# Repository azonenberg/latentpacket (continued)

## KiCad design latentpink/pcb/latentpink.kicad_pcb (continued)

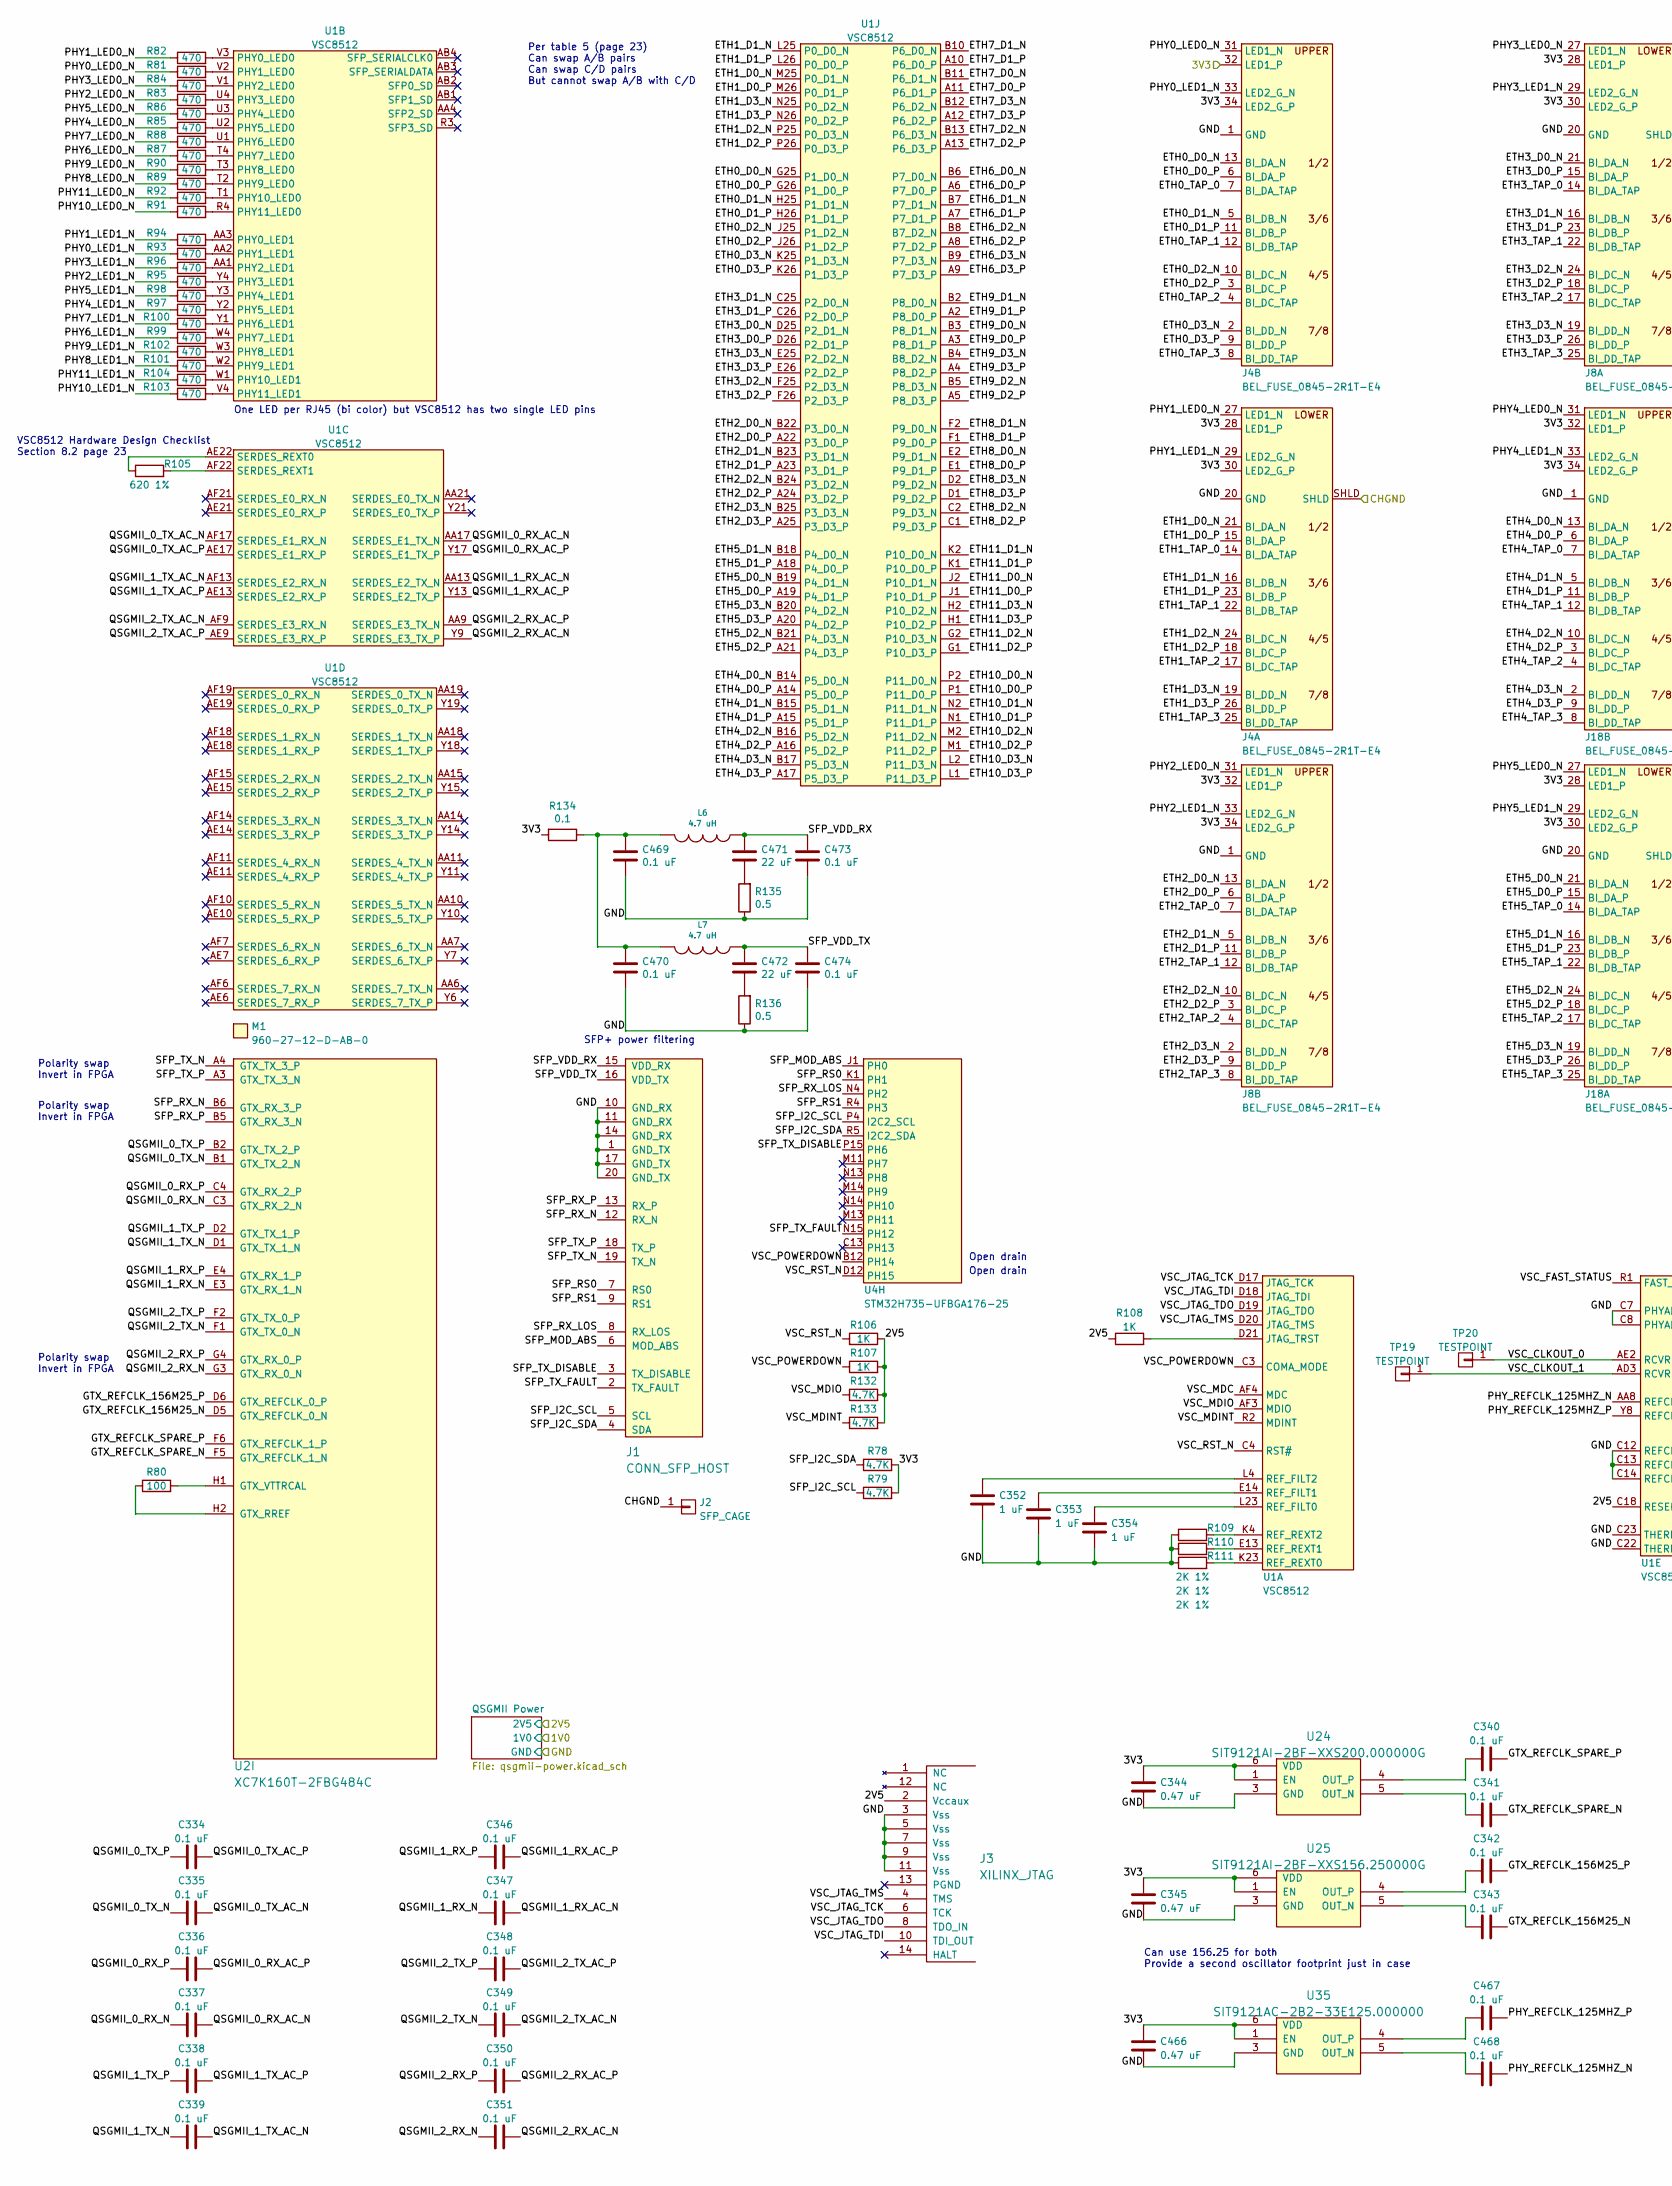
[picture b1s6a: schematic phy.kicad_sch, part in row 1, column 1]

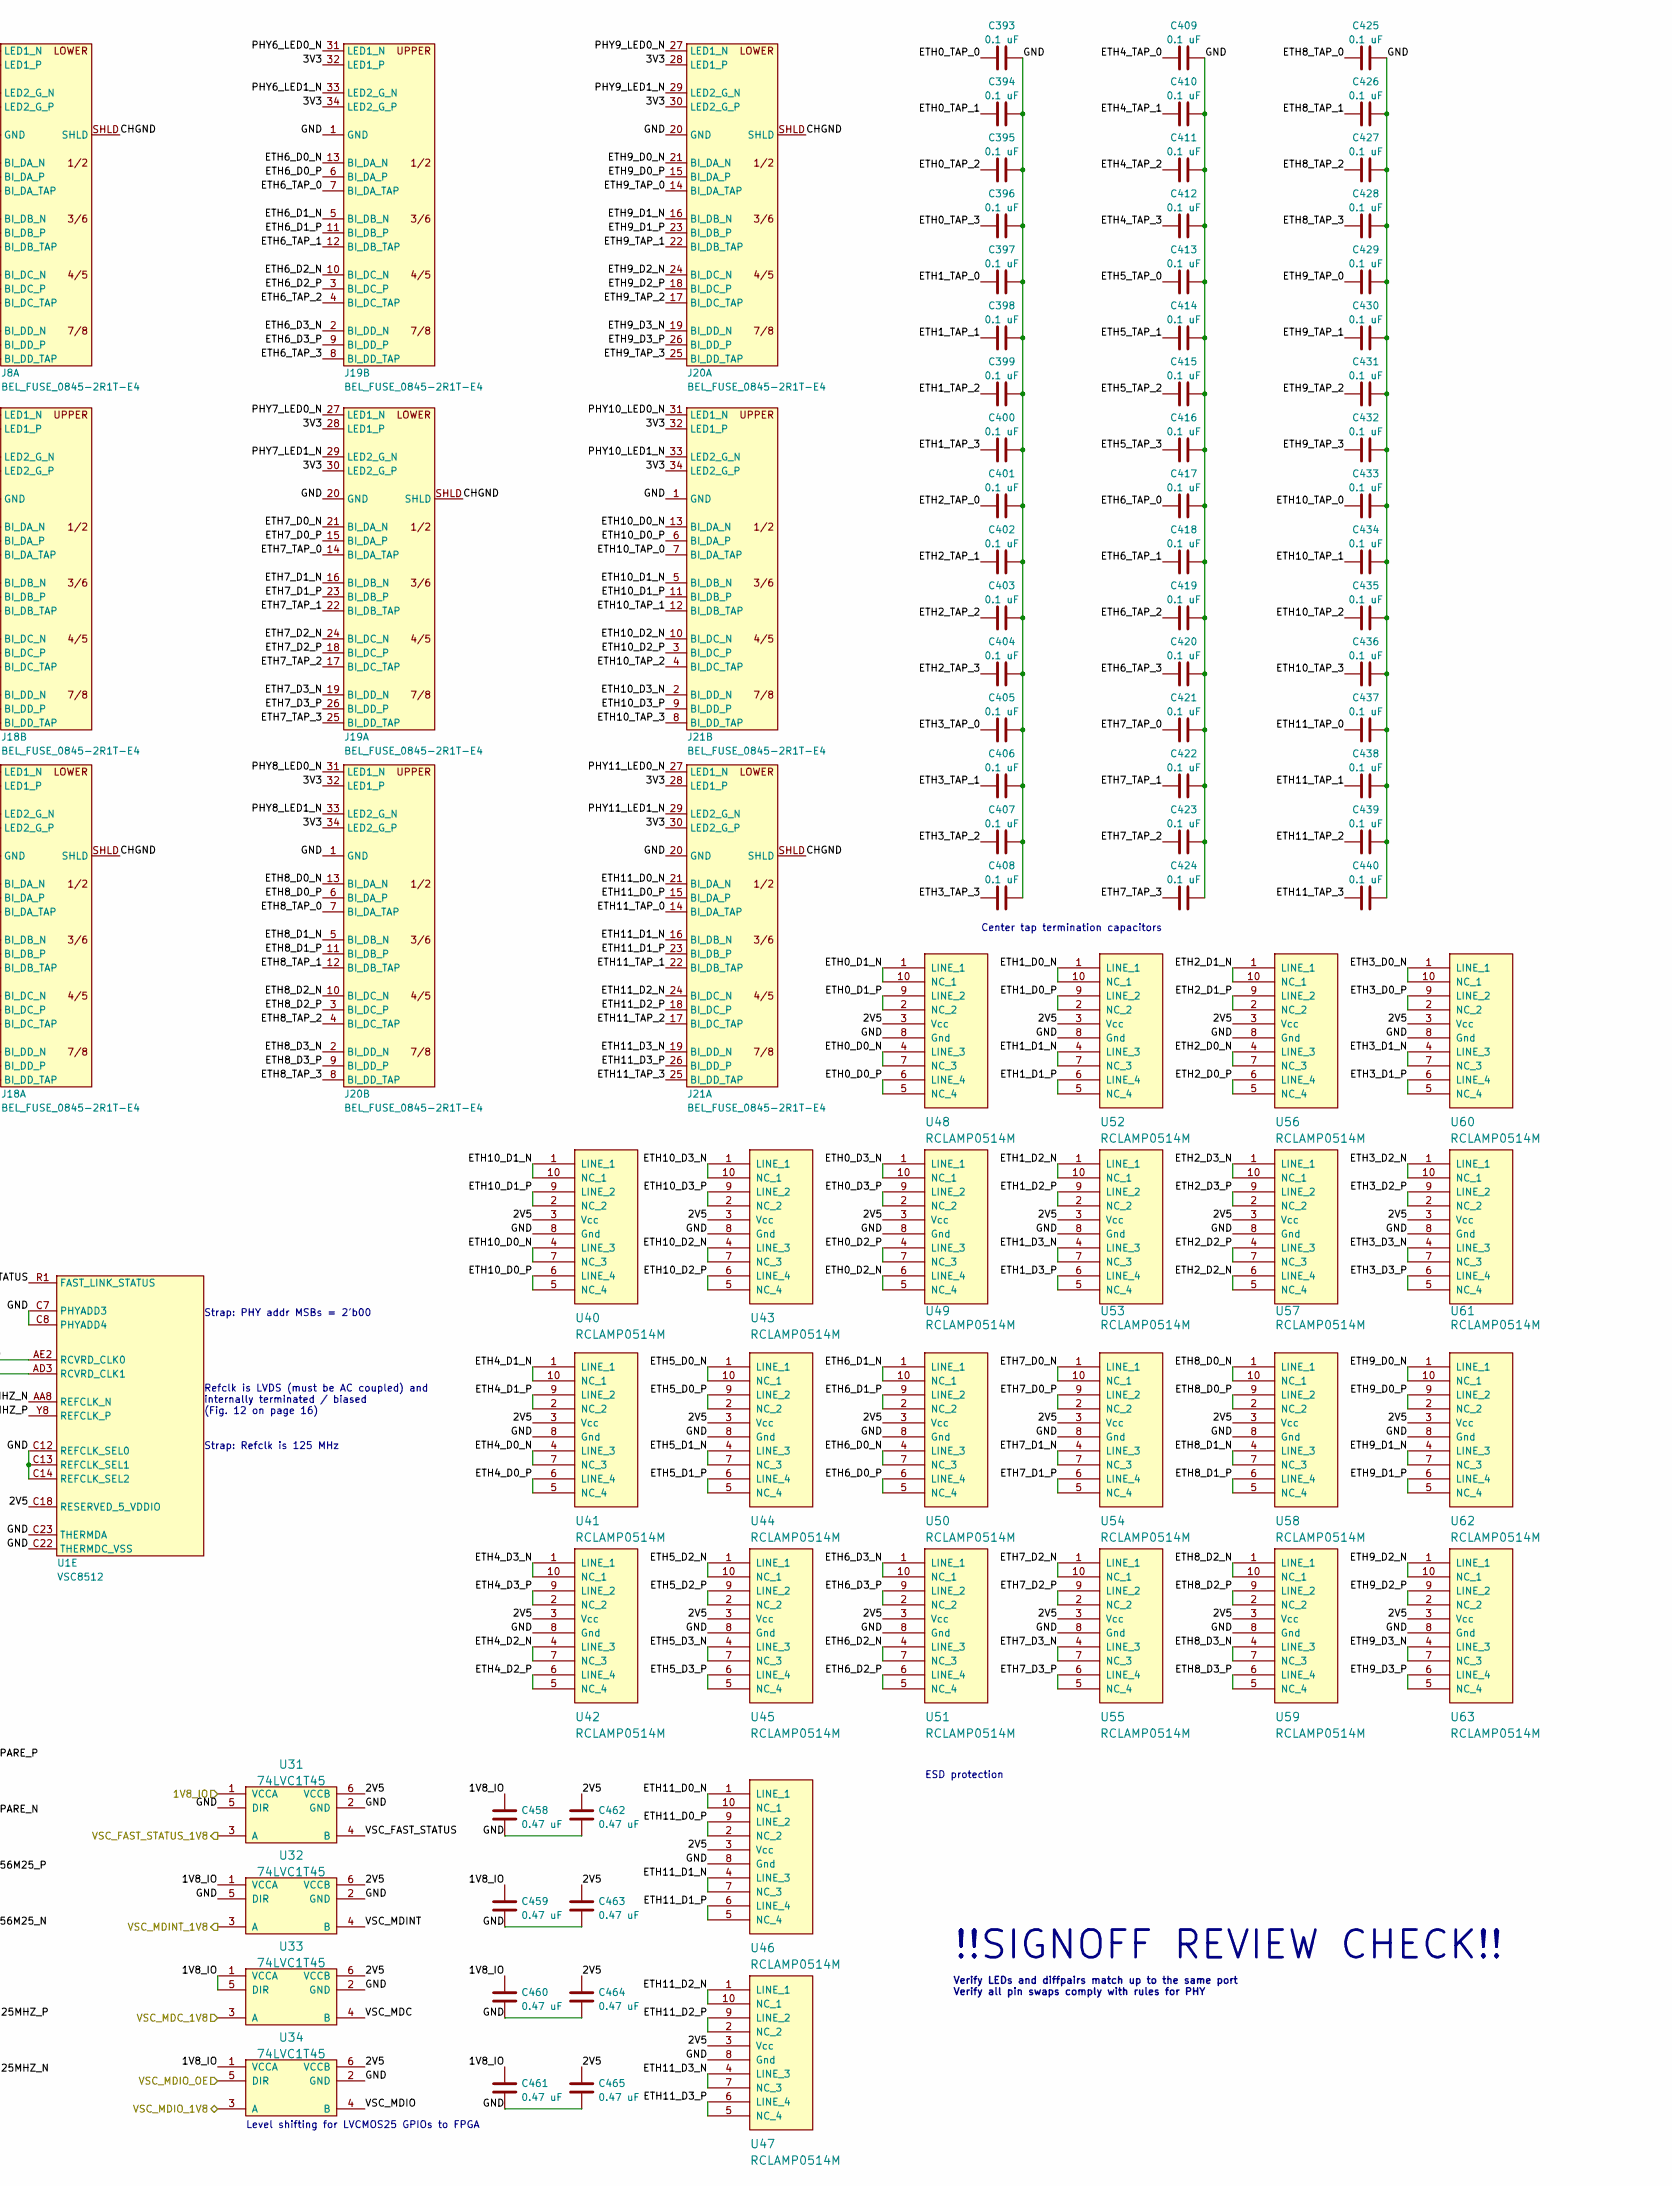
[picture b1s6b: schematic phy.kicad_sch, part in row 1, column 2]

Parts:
C334, C335, C336, C337, C338, C339, C340, C341, C342, C343, C346, C347, C348, C349, C350, C351, C393, C394, C395, C396, C397, C398, C399, C400, C401, C402, C403, C404, C405, C406, C407, C408, C409, C410, C411, C412, C413, C414, C415, C416, C417, C418, C419, C420, C421, C422, C423, C424, C425, C426, C427, C428, C429, C430, C431, C432, C433, C434, C435, C436, C437, C438, C439, C440, C467, C468, C469, C470, C473, C474: 0.1 uF; EIA_0402_CAP_NOSILK
C344, C345, C458, C459, C460, C461, C462, C463, C464, C465, C466: 0.47 uF; EIA_0402_CAP_NOSILK
C352, C353, C354: 1 uF; EIA_0402_CAP_NOSILK
C471, C472: 22 uF; EIA_1206_CAP_NOSILK
J1: CONN_SFP_HOST; CONN_SFP+_AMPHENOL_UE76_A10_2000T
J2: SFP_CAGE; CONN_SFP_CAGE_TE_2007194-1
J3: XILINX_JTAG; XILINX_JTAG_PTH_MOLEX_0878311420
J4, J8, J18, J19, J20, J21: BEL_FUSE_0845-2R1T-E4; CONN_RJ45_BELFUSE_0845-2R1T-E4
L6, L7: 4.7 uH; EIA_0805_INDUCTOR_NOSILK
M1: 960-27-12-D-AB-0; HEATSINK_WAKEFIELDVETTE_960-27-12-D-AB-0
R78, R79, R132, R133: 4.7K; EIA_0402_RES_NOSILK
R80: 100; EIA_0402_RES_NOSILK
R81, R82, R83, R84, R85, R86, R87, R88, R89, R90, R91, R92, R93, R94, R95, R96, R97, R98, R99, R100, R101, R102, R103, R104: 470; EIA_0402_RES_NOSILK
R105: 620 1%; EIA_0402_RES_NOSILK
R106, R107, R108: 1K; EIA_0402_RES_NOSILK
R109, R110, R111: 2K 1%; EIA_0402_RES_NOSILK
R134: 0.1; EIA_0402_RES_NOSILK
R135, R136: 0.5; EIA_0402_RES_NOSILK
TP19, TP20: TESTPOINT; TESTPOINT_SMT_0.5MM
U1: VSC8512; BGA_672_27x27_DEPOPCORNER_1MM
U2: XC7K160T-2FBG484C; BGA_484_22x22_FULLARRAY_1MM
U4: STM32H735-UFBGA176-25; BGA_201_10x10_DEPOP_0.65MM_OSHPARK
U24: SIT9121AI-2BF-XXS200.000000G; OSCILLATOR_LVDS_3.2x2.5
U25: SIT9121AI-2BF-XXS156.250000G; OSCILLATOR_LVDS_3.2x2.5
U31, U32, U33, U34: 74LVC1T45; DFN_6_0.5MM_1.45x1.00MM
U35: SIT9121AC-2B2-33E125.000000; OSCILLATOR_LVDS_3.2x2.5
U40, U41, U42, U43, U44, U45, U46, U47, U48, U49, U50, U51, U52, U53, U54, U55, U56, U57, U58, U59, U60, U61, U62, U63: RCLAMP0514M; SOP_10_0.5MM_3MM

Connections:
/1V8_IO: C458.1, C459.1, C460.1, C461.1, U31.1 (VCCA), U32.1 (VCCA), U33.1 (VCCA), U33.5 (DIR), U34.1 (VCCA); also elsewhere on the board
/2V5: C462.1, C463.1, C464.1, C465.1, J3.2 (Vccaux), R106.1, R107.2, R108.1, R132.2, R133.2, U1.C18 (RESERVED_5_VDDIO), U31.6 (VCCB), U32.6 (VCCB), U33.6 (VCCB), U34.6 (VCCB), U40.3 (Vcc), U41.3 (Vcc), U42.3 (Vcc), U43.3 (Vcc), U44.3 (Vcc), U45.3 (Vcc), U46.3 (Vcc), U47.3 (Vcc), U48.3 (Vcc), U49.3 (Vcc), U50.3 (Vcc), U51.3 (Vcc), U52.3 (Vcc), U53.3 (Vcc), U54.3 (Vcc), U55.3 (Vcc), U56.3 (Vcc), U57.3 (Vcc), U58.3 (Vcc), U59.3 (Vcc), U60.3 (Vcc), U61.3 (Vcc), U62.3 (Vcc), U63.3 (Vcc); also elsewhere on the board
/3V3: C344.1, C345.1, C466.1, J4.28 (LED1_P), J4.30 (LED2_G_P), J4.32 (LED1_P), J4.34 (LED2_G_P), J8.28 (LED1_P), J8.30 (LED2_G_P), J8.32 (LED1_P), J8.34 (LED2_G_P), J18.28 (LED1_P), J18.30 (LED2_G_P), J18.32 (LED1_P), J18.34 (LED2_G_P), J19.28 (LED1_P), J19.30 (LED2_G_P), J19.32 (LED1_P), J19.34 (LED2_G_P), J20.28 (LED1_P), J20.30 (LED2_G_P), J20.32 (LED1_P), J20.34 (LED2_G_P), J21.28 (LED1_P), J21.30 (LED2_G_P), J21.32 (LED1_P), J21.34 (LED2_G_P), R78.2, R79.2, R134.2, U24.1 (EN), U24.6 (VDD), U25.1 (EN), U25.6 (VDD), U35.1 (EN), U35.6 (VDD); also elsewhere on the board
/CHGND: J2.1, J4.SHLD, J8.SHLD, J18.SHLD, J19.SHLD, J20.SHLD, J21.SHLD; also elsewhere on the board
/GND: C344.2, C345.2, C352.2, C353.2, C354.2, C393.1, C394.1, C395.1, C396.1, C397.1, C398.1, C399.1, C400.1, C401.1, C402.1, C403.1, C404.1, C405.1, C406.1, C407.1, C408.1, C409.1, C410.1, C411.1, C412.1, C413.1, C414.1, C415.1, C416.1, C417.1, C418.1, C419.1, C420.1, C421.1, C422.1, C423.1, C424.1, C425.1, C426.1, C427.1, C428.1, C429.1, C430.1, C431.1, C432.1, C433.1, C434.1, C435.1, C436.1, C437.1, C438.1, C439.1, C440.1, C458.2, C459.2, C460.2, C461.2, C462.2, C463.2, C464.2, C465.2, C466.2, C469.2, C470.2, C473.2, C474.2, J1.1 (GND_TX), J1.10 (GND_RX), J1.11 (GND_RX), J1.14 (GND_RX), J1.17 (GND_TX), J1.20 (GND_TX), J3.3 (Vss), J3.5 (Vss), J3.7 (Vss), J3.9 (Vss), J3.11 (Vss), J4.1 (GND), J4.20 (GND), J8.1 (GND), J8.20 (GND), J18.1 (GND), J18.20 (GND), J19.1 (GND), J19.20 (GND), J20.1 (GND), J20.20 (GND), J21.1 (GND), J21.20 (GND), R109.1, R110.1, R111.1, R135.1, R136.1, U1.C7 (PHYADD3), U1.C8 (PHYADD4), U1.C12 (REFCLK_SEL0), U1.C13 (REFCLK_SEL1), U1.C14 (REFCLK_SEL2), U1.C22 (THERMDC_VSS), U1.C23 (THERMDA), U24.3 (GND), U25.3 (GND), U31.2 (GND), U31.5 (DIR), U32.2 (GND), U32.5 (DIR), U33.2 (GND), U34.2 (GND), U35.3 (GND), U40.8 (Gnd), U41.8 (Gnd), U42.8 (Gnd), U43.8 (Gnd), U44.8 (Gnd), U45.8 (Gnd), U46.8 (Gnd), U47.8 (Gnd), U48.8 (Gnd), U49.8 (Gnd), U50.8 (Gnd), U51.8 (Gnd), U52.8 (Gnd), U53.8 (Gnd), U54.8 (Gnd), U55.8 (Gnd), U56.8 (Gnd), U57.8 (Gnd), U58.8 (Gnd), U59.8 (Gnd), U60.8 (Gnd), U61.8 (Gnd), U62.8 (Gnd), U63.8 (Gnd); also elsewhere on the board
/QSGMII PHY/ETH0_D0_N: J4.13 (BI_DA_N), U1.G25 (P1_D0_N), U48.4 (LINE_3), U48.7 (NC_3)
/QSGMII PHY/ETH0_D0_P: J4.6 (BI_DA_P), U1.G26 (P1_D0_P), U48.5 (NC_4), U48.6 (LINE_4)
/QSGMII PHY/ETH0_D1_N: J4.5 (BI_DB_N), U1.H25 (P1_D1_N), U48.1 (LINE_1), U48.10 (NC_1)
/QSGMII PHY/ETH0_D1_P: J4.11 (BI_DB_P), U1.H26 (P1_D1_P), U48.2 (NC_2), U48.9 (LINE_2)
/QSGMII PHY/ETH0_D2_N: J4.10 (BI_DC_N), U1.J25 (P1_D2_N), U49.5 (NC_4), U49.6 (LINE_4)
/QSGMII PHY/ETH0_D2_P: J4.3 (BI_DC_P), U1.J26 (P1_D2_P), U49.4 (LINE_3), U49.7 (NC_3)
/QSGMII PHY/ETH0_D3_N: J4.2 (BI_DD_N), U1.K25 (P1_D3_N), U49.1 (LINE_1), U49.10 (NC_1)
/QSGMII PHY/ETH0_D3_P: J4.9 (BI_DD_P), U1.K26 (P1_D3_P), U49.2 (NC_2), U49.9 (LINE_2)
/QSGMII PHY/ETH0_TAP_0: C393.2, J4.7 (BI_DA_TAP)
/QSGMII PHY/ETH0_TAP_1: C394.2, J4.12 (BI_DB_TAP)
/QSGMII PHY/ETH0_TAP_2: C395.2, J4.4 (BI_DC_TAP)
/QSGMII PHY/ETH0_TAP_3: C396.2, J4.8 (BI_DD_TAP)
/QSGMII PHY/ETH1_D0_N: J4.21 (BI_DA_N), U1.M25 (P0_D1_N), U52.1 (LINE_1), U52.10 (NC_1)
/QSGMII PHY/ETH1_D0_P: J4.15 (BI_DA_P), U1.M26 (P0_D1_P), U52.2 (NC_2), U52.9 (LINE_2)
/QSGMII PHY/ETH1_D1_N: J4.16 (BI_DB_N), U1.L25 (P0_D0_N), U52.4 (LINE_3), U52.7 (NC_3)
/QSGMII PHY/ETH1_D1_P: J4.23 (BI_DB_P), U1.L26 (P0_D0_P), U52.5 (NC_4), U52.6 (LINE_4)
/QSGMII PHY/ETH1_D2_N: J4.24 (BI_DC_N), U1.P25 (P0_D3_N), U53.1 (LINE_1), U53.10 (NC_1)
/QSGMII PHY/ETH1_D2_P: J4.18 (BI_DC_P), U1.P26 (P0_D3_P), U53.2 (NC_2), U53.9 (LINE_2)
/QSGMII PHY/ETH1_D3_N: J4.19 (BI_DD_N), U1.N25 (P0_D2_N), U53.4 (LINE_3), U53.7 (NC_3)
/QSGMII PHY/ETH1_D3_P: J4.26 (BI_DD_P), U1.N26 (P0_D2_P), U53.5 (NC_4), U53.6 (LINE_4)
/QSGMII PHY/ETH1_TAP_0: C397.2, J4.14 (BI_DA_TAP)
/QSGMII PHY/ETH1_TAP_1: C398.2, J4.22 (BI_DB_TAP)
/QSGMII PHY/ETH1_TAP_2: C399.2, J4.17 (BI_DC_TAP)
/QSGMII PHY/ETH1_TAP_3: C400.2, J4.25 (BI_DD_TAP)
/QSGMII PHY/ETH2_D0_N: J8.13 (BI_DA_N), U1.B22 (P3_D0_N), U56.4 (LINE_3), U56.7 (NC_3)
/QSGMII PHY/ETH2_D0_P: J8.6 (BI_DA_P), U1.A22 (P3_D0_P), U56.5 (NC_4), U56.6 (LINE_4)
/QSGMII PHY/ETH2_D1_N: J8.5 (BI_DB_N), U1.B23 (P3_D1_N), U56.1 (LINE_1), U56.10 (NC_1)
/QSGMII PHY/ETH2_D1_P: J8.11 (BI_DB_P), U1.A23 (P3_D1_P), U56.2 (NC_2), U56.9 (LINE_2)
/QSGMII PHY/ETH2_D2_N: J8.10 (BI_DC_N), U1.B24 (P3_D2_N), U57.5 (NC_4), U57.6 (LINE_4)
/QSGMII PHY/ETH2_D2_P: J8.3 (BI_DC_P), U1.A24 (P3_D2_P), U57.4 (LINE_3), U57.7 (NC_3)
/QSGMII PHY/ETH2_D3_N: J8.2 (BI_DD_N), U1.B25 (P3_D3_N), U57.1 (LINE_1), U57.10 (NC_1)
/QSGMII PHY/ETH2_D3_P: J8.9 (BI_DD_P), U1.A25 (P3_D3_P), U57.2 (NC_2), U57.9 (LINE_2)
/QSGMII PHY/ETH2_TAP_0: C401.2, J8.7 (BI_DA_TAP)
/QSGMII PHY/ETH2_TAP_1: C402.2, J8.12 (BI_DB_TAP)
/QSGMII PHY/ETH2_TAP_2: C403.2, J8.4 (BI_DC_TAP)
/QSGMII PHY/ETH2_TAP_3: C404.2, J8.8 (BI_DD_TAP)
/QSGMII PHY/ETH3_D0_N: J8.21 (BI_DA_N), U1.D25 (P2_D1_N), U60.1 (LINE_1), U60.10 (NC_1)
/QSGMII PHY/ETH3_D0_P: J8.15 (BI_DA_P), U1.D26 (P2_D1_P), U60.2 (NC_2), U60.9 (LINE_2)
/QSGMII PHY/ETH3_D1_N: J8.16 (BI_DB_N), U1.C25 (P2_D0_N), U60.4 (LINE_3), U60.7 (NC_3)
/QSGMII PHY/ETH3_D1_P: J8.23 (BI_DB_P), U1.C26 (P2_D0_P), U60.5 (NC_4), U60.6 (LINE_4)
/QSGMII PHY/ETH3_D2_N: J8.24 (BI_DC_N), U1.F25 (P2_D3_N), U61.1 (LINE_1), U61.10 (NC_1)
/QSGMII PHY/ETH3_D2_P: J8.18 (BI_DC_P), U1.F26 (P2_D3_P), U61.2 (NC_2), U61.9 (LINE_2)
/QSGMII PHY/ETH3_D3_N: J8.19 (BI_DD_N), U1.E25 (P2_D2_N), U61.4 (LINE_3), U61.7 (NC_3)
/QSGMII PHY/ETH3_D3_P: J8.26 (BI_DD_P), U1.E26 (P2_D2_P), U61.5 (NC_4), U61.6 (LINE_4)
/QSGMII PHY/ETH3_TAP_0: C405.2, J8.14 (BI_DA_TAP)
/QSGMII PHY/ETH3_TAP_1: C406.2, J8.22 (BI_DB_TAP)
/QSGMII PHY/ETH3_TAP_2: C407.2, J8.17 (BI_DC_TAP)
/QSGMII PHY/ETH3_TAP_3: C408.2, J8.25 (BI_DD_TAP)
/QSGMII PHY/ETH4_D0_N: J18.13 (BI_DA_N), U1.B14 (P5_D0_N), U41.4 (LINE_3), U41.7 (NC_3)
/QSGMII PHY/ETH4_D0_P: J18.6 (BI_DA_P), U1.A14 (P5_D0_P), U41.5 (NC_4), U41.6 (LINE_4)
/QSGMII PHY/ETH4_D1_N: J18.5 (BI_DB_N), U1.B15 (P5_D1_N), U41.1 (LINE_1), U41.10 (NC_1)
/QSGMII PHY/ETH4_D1_P: J18.11 (BI_DB_P), U1.A15 (P5_D1_P), U41.2 (NC_2), U41.9 (LINE_2)
/QSGMII PHY/ETH4_D2_N: J18.10 (BI_DC_N), U1.B16 (P5_D2_N), U42.4 (LINE_3), U42.7 (NC_3)
/QSGMII PHY/ETH4_D2_P: J18.3 (BI_DC_P), U1.A16 (P5_D2_P), U42.5 (NC_4), U42.6 (LINE_4)
/QSGMII PHY/ETH4_D3_N: J18.2 (BI_DD_N), U1.B17 (P5_D3_N), U42.1 (LINE_1), U42.10 (NC_1)
/QSGMII PHY/ETH4_D3_P: J18.9 (BI_DD_P), U1.A17 (P5_D3_P), U42.2 (NC_2), U42.9 (LINE_2)
/QSGMII PHY/ETH4_TAP_0: C409.2, J18.7 (BI_DA_TAP)
/QSGMII PHY/ETH4_TAP_1: C410.2, J18.12 (BI_DB_TAP)
/QSGMII PHY/ETH4_TAP_2: C411.2, J18.4 (BI_DC_TAP)
/QSGMII PHY/ETH4_TAP_3: C412.2, J18.8 (BI_DD_TAP)
/QSGMII PHY/ETH5_D0_N: J18.21 (BI_DA_N), U1.B19 (P4_D1_N), U44.1 (LINE_1), U44.10 (NC_1)
/QSGMII PHY/ETH5_D0_P: J18.15 (BI_DA_P), U1.A19 (P4_D1_P), U44.2 (NC_2), U44.9 (LINE_2)
/QSGMII PHY/ETH5_D1_N: J18.16 (BI_DB_N), U1.B18 (P4_D0_N), U44.4 (LINE_3), U44.7 (NC_3)
/QSGMII PHY/ETH5_D1_P: J18.23 (BI_DB_P), U1.A18 (P4_D0_P), U44.5 (NC_4), U44.6 (LINE_4)
/QSGMII PHY/ETH5_D2_N: J18.24 (BI_DC_N), U1.B21 (P4_D3_N), U45.1 (LINE_1), U45.10 (NC_1)
/QSGMII PHY/ETH5_D2_P: J18.18 (BI_DC_P), U1.A21 (P4_D3_P), U45.2 (NC_2), U45.9 (LINE_2)
/QSGMII PHY/ETH5_D3_N: J18.19 (BI_DD_N), U1.B20 (P4_D2_N), U45.4 (LINE_3), U45.7 (NC_3)
/QSGMII PHY/ETH5_D3_P: J18.26 (BI_DD_P), U1.A20 (P4_D2_P), U45.5 (NC_4), U45.6 (LINE_4)
/QSGMII PHY/ETH5_TAP_0: C413.2, J18.14 (BI_DA_TAP)
/QSGMII PHY/ETH5_TAP_1: C414.2, J18.22 (BI_DB_TAP)
/QSGMII PHY/ETH5_TAP_2: C415.2, J18.17 (BI_DC_TAP)
/QSGMII PHY/ETH5_TAP_3: C416.2, J18.25 (BI_DD_TAP)
/QSGMII PHY/ETH6_D0_N: J19.13 (BI_DA_N), U1.B6 (P7_D0_N), U50.4 (LINE_3), U50.7 (NC_3)
/QSGMII PHY/ETH6_D0_P: J19.6 (BI_DA_P), U1.A6 (P7_D0_P), U50.5 (NC_4), U50.6 (LINE_4)
/QSGMII PHY/ETH6_D1_N: J19.5 (BI_DB_N), U1.B7 (P7_D1_N), U50.1 (LINE_1), U50.10 (NC_1)
/QSGMII PHY/ETH6_D1_P: J19.11 (BI_DB_P), U1.A7 (P7_D1_P), U50.2 (NC_2), U50.9 (LINE_2)
/QSGMII PHY/ETH6_D2_N: J19.10 (BI_DC_N), U1.B8 (B7_D2_N), U51.4 (LINE_3), U51.7 (NC_3)
/QSGMII PHY/ETH6_D2_P: J19.3 (BI_DC_P), U1.A8 (P7_D2_P), U51.5 (NC_4), U51.6 (LINE_4)
/QSGMII PHY/ETH6_D3_N: J19.2 (BI_DD_N), U1.B9 (P7_D3_N), U51.1 (LINE_1), U51.10 (NC_1)
/QSGMII PHY/ETH6_D3_P: J19.9 (BI_DD_P), U1.A9 (P7_D3_P), U51.2 (NC_2), U51.9 (LINE_2)
/QSGMII PHY/ETH6_TAP_0: C417.2, J19.7 (BI_DA_TAP)
/QSGMII PHY/ETH6_TAP_1: C418.2, J19.12 (BI_DB_TAP)
/QSGMII PHY/ETH6_TAP_2: C419.2, J19.4 (BI_DC_TAP)
/QSGMII PHY/ETH6_TAP_3: C420.2, J19.8 (BI_DD_TAP)
/QSGMII PHY/ETH7_D0_N: J19.21 (BI_DA_N), U1.B11 (P6_D1_N), U54.1 (LINE_1), U54.10 (NC_1)
/QSGMII PHY/ETH7_D0_P: J19.15 (BI_DA_P), U1.A11 (P6_D1_P), U54.2 (NC_2), U54.9 (LINE_2)
/QSGMII PHY/ETH7_D1_N: J19.16 (BI_DB_N), U1.B10 (P6_D0_N), U54.4 (LINE_3), U54.7 (NC_3)
/QSGMII PHY/ETH7_D1_P: J19.23 (BI_DB_P), U1.A10 (P6_D0_P), U54.5 (NC_4), U54.6 (LINE_4)
/QSGMII PHY/ETH7_D2_N: J19.24 (BI_DC_N), U1.B13 (P6_D3_N), U55.1 (LINE_1), U55.10 (NC_1)
/QSGMII PHY/ETH7_D2_P: J19.18 (BI_DC_P), U1.A13 (P6_D3_P), U55.2 (NC_2), U55.9 (LINE_2)
/QSGMII PHY/ETH7_D3_N: J19.19 (BI_DD_N), U1.B12 (P6_D2_N), U55.4 (LINE_3), U55.7 (NC_3)
/QSGMII PHY/ETH7_D3_P: J19.26 (BI_DD_P), U1.A12 (P6_D2_P), U55.5 (NC_4), U55.6 (LINE_4)
/QSGMII PHY/ETH7_TAP_0: C421.2, J19.14 (BI_DA_TAP)
/QSGMII PHY/ETH7_TAP_1: C422.2, J19.22 (BI_DB_TAP)
/QSGMII PHY/ETH7_TAP_2: C423.2, J19.17 (BI_DC_TAP)
/QSGMII PHY/ETH7_TAP_3: C424.2, J19.25 (BI_DD_TAP)
/QSGMII PHY/ETH8_D0_N: J20.13 (BI_DA_N), U1.E2 (P9_D1_N), U58.1 (LINE_1), U58.10 (NC_1)
/QSGMII PHY/ETH8_D0_P: J20.6 (BI_DA_P), U1.E1 (P9_D1_P), U58.2 (NC_2), U58.9 (LINE_2)
/QSGMII PHY/ETH8_D1_N: J20.5 (BI_DB_N), U1.F2 (P9_D0_N), U58.4 (LINE_3), U58.7 (NC_3)
/QSGMII PHY/ETH8_D1_P: J20.11 (BI_DB_P), U1.F1 (P9_D0_P), U58.5 (NC_4), U58.6 (LINE_4)
/QSGMII PHY/ETH8_D2_N: J20.10 (BI_DC_N), U1.C2 (P9_D3_N), U59.1 (LINE_1), U59.10 (NC_1)
/QSGMII PHY/ETH8_D2_P: J20.3 (BI_DC_P), U1.C1 (P9_D3_P), U59.2 (NC_2), U59.9 (LINE_2)
/QSGMII PHY/ETH8_D3_N: J20.2 (BI_DD_N), U1.D2 (P9_D2_N), U59.4 (LINE_3), U59.7 (NC_3)
/QSGMII PHY/ETH8_D3_P: J20.9 (BI_DD_P), U1.D1 (P9_D2_P), U59.5 (NC_4), U59.6 (LINE_4)
/QSGMII PHY/ETH8_TAP_0: C425.2, J20.7 (BI_DA_TAP)
/QSGMII PHY/ETH8_TAP_1: C426.2, J20.12 (BI_DB_TAP)
/QSGMII PHY/ETH8_TAP_2: C427.2, J20.4 (BI_DC_TAP)
/QSGMII PHY/ETH8_TAP_3: C428.2, J20.8 (BI_DD_TAP)
/QSGMII PHY/ETH9_D0_N: J20.21 (BI_DA_N), U1.B3 (P8_D1_N), U62.1 (LINE_1), U62.10 (NC_1)
/QSGMII PHY/ETH9_D0_P: J20.15 (BI_DA_P), U1.A3 (P8_D1_P), U62.2 (NC_2), U62.9 (LINE_2)
/QSGMII PHY/ETH9_D1_N: J20.16 (BI_DB_N), U1.B2 (P8_D0_N), U62.4 (LINE_3), U62.7 (NC_3)
/QSGMII PHY/ETH9_D1_P: J20.23 (BI_DB_P), U1.A2 (P8_D0_P), U62.5 (NC_4), U62.6 (LINE_4)
/QSGMII PHY/ETH9_D2_N: J20.24 (BI_DC_N), U1.B5 (P8_D3_N), U63.1 (LINE_1), U63.10 (NC_1)
/QSGMII PHY/ETH9_D2_P: J20.18 (BI_DC_P), U1.A5 (P8_D3_P), U63.2 (NC_2), U63.9 (LINE_2)
/QSGMII PHY/ETH9_D3_N: J20.19 (BI_DD_N), U1.B4 (B8_D2_N), U63.4 (LINE_3), U63.7 (NC_3)
/QSGMII PHY/ETH9_D3_P: J20.26 (BI_DD_P), U1.A4 (P8_D2_P), U63.5 (NC_4), U63.6 (LINE_4)
/QSGMII PHY/ETH9_TAP_0: C429.2, J20.14 (BI_DA_TAP)
/QSGMII PHY/ETH9_TAP_1: C430.2, J20.22 (BI_DB_TAP)
/QSGMII PHY/ETH9_TAP_2: C431.2, J20.17 (BI_DC_TAP)
/QSGMII PHY/ETH9_TAP_3: C432.2, J20.25 (BI_DD_TAP)
/QSGMII PHY/ETH10_D0_N: J21.13 (BI_DA_N), U1.P2 (P11_D0_N), U40.4 (LINE_3), U40.7 (NC_3)
/QSGMII PHY/ETH10_D0_P: J21.6 (BI_DA_P), U1.P1 (P11_D0_P), U40.5 (NC_4), U40.6 (LINE_4)
/QSGMII PHY/ETH10_D1_N: J21.5 (BI_DB_N), U1.N2 (P11_D1_N), U40.1 (LINE_1), U40.10 (NC_1)
/QSGMII PHY/ETH10_D1_P: J21.11 (BI_DB_P), U1.N1 (P11_D1_P), U40.2 (NC_2), U40.9 (LINE_2)
/QSGMII PHY/ETH10_D2_N: J21.10 (BI_DC_N), U1.M2 (P11_D2_N), U43.4 (LINE_3), U43.7 (NC_3)
/QSGMII PHY/ETH10_D2_P: J21.3 (BI_DC_P), U1.M1 (P11_D2_P), U43.5 (NC_4), U43.6 (LINE_4)
/QSGMII PHY/ETH10_D3_N: J21.2 (BI_DD_N), U1.L2 (P11_D3_N), U43.1 (LINE_1), U43.10 (NC_1)
/QSGMII PHY/ETH10_D3_P: J21.9 (BI_DD_P), U1.L1 (P11_D3_P), U43.2 (NC_2), U43.9 (LINE_2)
/QSGMII PHY/ETH10_TAP_0: C433.2, J21.7 (BI_DA_TAP)
/QSGMII PHY/ETH10_TAP_1: C434.2, J21.12 (BI_DB_TAP)
/QSGMII PHY/ETH10_TAP_2: C435.2, J21.4 (BI_DC_TAP)
/QSGMII PHY/ETH10_TAP_3: C436.2, J21.8 (BI_DD_TAP)
/QSGMII PHY/ETH11_D0_N: J21.21 (BI_DA_N), U1.J2 (P10_D1_N), U46.1 (LINE_1), U46.10 (NC_1)
/QSGMII PHY/ETH11_D0_P: J21.15 (BI_DA_P), U1.J1 (P10_D1_P), U46.2 (NC_2), U46.9 (LINE_2)
/QSGMII PHY/ETH11_D1_N: J21.16 (BI_DB_N), U1.K2 (P10_D0_N), U46.4 (LINE_3), U46.7 (NC_3)
/QSGMII PHY/ETH11_D1_P: J21.23 (BI_DB_P), U1.K1 (P10_D0_P), U46.5 (NC_4), U46.6 (LINE_4)
/QSGMII PHY/ETH11_D2_N: J21.24 (BI_DC_N), U1.G2 (P10_D3_N), U47.1 (LINE_1), U47.10 (NC_1)
/QSGMII PHY/ETH11_D2_P: J21.18 (BI_DC_P), U1.G1 (P10_D3_P), U47.2 (NC_2), U47.9 (LINE_2)
/QSGMII PHY/ETH11_D3_N: J21.19 (BI_DD_N), U1.H2 (P10_D2_N), U47.4 (LINE_3), U47.7 (NC_3)
/QSGMII PHY/ETH11_D3_P: J21.26 (BI_DD_P), U1.H1 (P10_D2_P), U47.5 (NC_4), U47.6 (LINE_4)
/QSGMII PHY/ETH11_TAP_0: C437.2, J21.14 (BI_DA_TAP)
/QSGMII PHY/ETH11_TAP_1: C438.2, J21.22 (BI_DB_TAP)
/QSGMII PHY/ETH11_TAP_2: C439.2, J21.17 (BI_DC_TAP)
/QSGMII PHY/ETH11_TAP_3: C440.2, J21.25 (BI_DD_TAP)
/QSGMII PHY/GTX_REFCLK_156M25_N: C343.2, U2.D5 (GTX_REFCLK_0_N)
/QSGMII PHY/GTX_REFCLK_156M25_P: C342.2, U2.D6 (GTX_REFCLK_0_P)
/QSGMII PHY/GTX_REFCLK_SPARE_N: C341.2, U2.F5 (GTX_REFCLK_1_N)
/QSGMII PHY/GTX_REFCLK_SPARE_P: C340.2, U2.F6 (GTX_REFCLK_1_P)
/QSGMII PHY/PHY0_LED0_N: J4.31 (LED1_N), R81.1
/QSGMII PHY/PHY0_LED1_N: J4.33 (LED2_G_N), R93.1
/QSGMII PHY/PHY1_LED0_N: J4.27 (LED1_N), R82.1
/QSGMII PHY/PHY1_LED1_N: J4.29 (LED2_G_N), R94.1
/QSGMII PHY/PHY2_LED0_N: J8.31 (LED1_N), R83.1
/QSGMII PHY/PHY2_LED1_N: J8.33 (LED2_G_N), R95.1
/QSGMII PHY/PHY3_LED0_N: J8.27 (LED1_N), R84.1
/QSGMII PHY/PHY3_LED1_N: J8.29 (LED2_G_N), R96.1
/QSGMII PHY/PHY4_LED0_N: J18.31 (LED1_N), R85.1
/QSGMII PHY/PHY4_LED1_N: J18.33 (LED2_G_N), R97.1
/QSGMII PHY/PHY5_LED0_N: J18.27 (LED1_N), R86.1
/QSGMII PHY/PHY5_LED1_N: J18.29 (LED2_G_N), R98.1
/QSGMII PHY/PHY6_LED0_N: J19.31 (LED1_N), R87.1
/QSGMII PHY/PHY6_LED1_N: J19.33 (LED2_G_N), R99.1
/QSGMII PHY/PHY7_LED0_N: J19.27 (LED1_N), R88.1
/QSGMII PHY/PHY7_LED1_N: J19.29 (LED2_G_N), R100.1
/QSGMII PHY/PHY8_LED0_N: J20.31 (LED1_N), R89.1
/QSGMII PHY/PHY8_LED1_N: J20.33 (LED2_G_N), R101.1
/QSGMII PHY/PHY9_LED0_N: J20.27 (LED1_N), R90.1
/QSGMII PHY/PHY9_LED1_N: J20.29 (LED2_G_N), R102.1
/QSGMII PHY/PHY10_LED0_N: J21.31 (LED1_N), R91.1
/QSGMII PHY/PHY10_LED1_N: J21.33 (LED2_G_N), R103.1
/QSGMII PHY/PHY11_LED0_N: J21.27 (LED1_N), R92.1
/QSGMII PHY/PHY11_LED1_N: J21.29 (LED2_G_N), R104.1
/QSGMII PHY/PHY_REFCLK_125MHZ_N: C468.2, U1.AA8 (REFCLK_N)
/QSGMII PHY/PHY_REFCLK_125MHZ_P: C467.2, U1.Y8 (REFCLK_P)
/QSGMII PHY/QSGMII_0_RX_AC_N: C337.2, U1.AA17 (SERDES_E1_TX_N)
/QSGMII PHY/QSGMII_0_RX_AC_P: C336.2, U1.Y17 (SERDES_E1_TX_P)
/QSGMII PHY/QSGMII_0_RX_N: C337.1, U2.C3 (GTX_RX_2_N)
/QSGMII PHY/QSGMII_0_RX_P: C336.1, U2.C4 (GTX_RX_2_P)
/QSGMII PHY/QSGMII_0_TX_AC_N: C335.2, U1.AF17 (SERDES_E1_RX_N)
/QSGMII PHY/QSGMII_0_TX_AC_P: C334.2, U1.AE17 (SERDES_E1_RX_P)
/QSGMII PHY/QSGMII_0_TX_N: C335.1, U2.B1 (GTX_TX_2_N)
/QSGMII PHY/QSGMII_0_TX_P: C334.1, U2.B2 (GTX_TX_2_P)
/QSGMII PHY/QSGMII_1_RX_AC_N: C347.2, U1.AA13 (SERDES_E2_TX_N)
/QSGMII PHY/QSGMII_1_RX_AC_P: C346.2, U1.Y13 (SERDES_E2_TX_P)
/QSGMII PHY/QSGMII_1_RX_N: C347.1, U2.E3 (GTX_RX_1_N)
/QSGMII PHY/QSGMII_1_RX_P: C346.1, U2.E4 (GTX_RX_1_P)
/QSGMII PHY/QSGMII_1_TX_AC_N: C339.2, U1.AF13 (SERDES_E2_RX_N)
/QSGMII PHY/QSGMII_1_TX_AC_P: C338.2, U1.AE13 (SERDES_E2_RX_P)
/QSGMII PHY/QSGMII_1_TX_N: C339.1, U2.D1 (GTX_TX_1_N)
/QSGMII PHY/QSGMII_1_TX_P: C338.1, U2.D2 (GTX_TX_1_P)
/QSGMII PHY/QSGMII_2_RX_AC_N: C351.2, U1.Y9 (SERDES_E3_TX_P)
/QSGMII PHY/QSGMII_2_RX_AC_P: C350.2, U1.AA9 (SERDES_E3_TX_N)
/QSGMII PHY/QSGMII_2_RX_N: C351.1, U2.G3 (GTX_RX_0_N)
/QSGMII PHY/QSGMII_2_RX_P: C350.1, U2.G4 (GTX_RX_0_P)
/QSGMII PHY/QSGMII_2_TX_AC_N: C349.2, U1.AF9 (SERDES_E3_RX_N)
/QSGMII PHY/QSGMII_2_TX_AC_P: C348.2, U1.AE9 (SERDES_E3_RX_P)
/QSGMII PHY/QSGMII_2_TX_N: C349.1, U2.F1 (GTX_TX_0_N)
/QSGMII PHY/QSGMII_2_TX_P: C348.1, U2.F2 (GTX_TX_0_P)
/QSGMII PHY/SFP_I2C_SCL: J1.5 (SCL), R79.1, U4.P4 (I2C2_SCL)
/QSGMII PHY/SFP_I2C_SDA: J1.4 (SDA), R78.1, U4.R5 (I2C2_SDA)
/QSGMII PHY/SFP_MOD_ABS: J1.6 (MOD_ABS), U4.J1 (PH0)
/QSGMII PHY/SFP_RS0: J1.7 (RS0), U4.K1 (PH1)
/QSGMII PHY/SFP_RS1: J1.9 (RS1), U4.R4 (PH3)
/QSGMII PHY/SFP_RX_LOS: J1.8 (RX_LOS), U4.N4 (PH2)
/QSGMII PHY/SFP_RX_N: J1.12 (RX_N), U2.B6 (GTX_RX_3_P)
/QSGMII PHY/SFP_RX_P: J1.13 (RX_P), U2.B5 (GTX_RX_3_N)
/QSGMII PHY/SFP_TX_DISABLE: J1.3 (TX_DISABLE), U4.P15 (PH6)
/QSGMII PHY/SFP_TX_FAULT: J1.2 (TX_FAULT), U4.N15 (PH12)
/QSGMII PHY/SFP_TX_N: J1.19 (TX_N), U2.A4 (GTX_TX_3_P)
/QSGMII PHY/SFP_TX_P: J1.18 (TX_P), U2.A3 (GTX_TX_3_N)
/QSGMII PHY/SFP_VDD_RX: C471.1, C473.1, J1.15 (VDD_RX), L6.1
/QSGMII PHY/SFP_VDD_TX: C472.1, C474.1, J1.16 (VDD_TX), L7.1
/QSGMII PHY/VSC_CLKOUT_0: TP20.1, U1.AE2 (RCVRD_CLK0)
/QSGMII PHY/VSC_CLKOUT_1: TP19.1, U1.AD3 (RCVRD_CLK1)
/QSGMII PHY/VSC_FAST_STATUS: U1.R1 (FAST_LINK_STATUS), U31.4 (B)
/QSGMII PHY/VSC_FAST_STATUS_1V8: U31.3 (A); also elsewhere on the board
/QSGMII PHY/VSC_JTAG_TCK: J3.6 (TCK), U1.D17 (JTAG_TCK)
/QSGMII PHY/VSC_JTAG_TDI: J3.10 (TDI_OUT), U1.D18 (JTAG_TDI)
/QSGMII PHY/VSC_JTAG_TDO: J3.8 (TDO_IN), U1.D19 (JTAG_TDO)
/QSGMII PHY/VSC_JTAG_TMS: J3.4 (TMS), U1.D20 (JTAG_TMS)
/QSGMII PHY/VSC_MDC: U1.AF4 (MDC), U33.4 (B)
/QSGMII PHY/VSC_MDC_1V8: U33.3 (A); also elsewhere on the board
/QSGMII PHY/VSC_MDINT: R133.1, U1.R2 (MDINT), U32.4 (B)
/QSGMII PHY/VSC_MDINT_1V8: U32.3 (A); also elsewhere on the board
/QSGMII PHY/VSC_MDIO: R132.1, U1.AF3 (MDIO), U34.4 (B)
/QSGMII PHY/VSC_MDIO_1V8: U34.3 (A); also elsewhere on the board
/QSGMII PHY/VSC_MDIO_OE: U34.5 (DIR); also elsewhere on the board
/QSGMII PHY/VSC_POWERDOWN: R107.1, U1.C3 (COMA_MODE), U4.B12 (PH14)
/QSGMII PHY/VSC_RST_N: R106.2, U1.C4 (RST#), U4.D12 (PH15)
unnamed: C340.1, U24.4 (OUT_P)
unnamed: C341.1, U24.5 (OUT_N)
unnamed: C342.1, U25.4 (OUT_P)
unnamed: C343.1, U25.5 (OUT_N)
unnamed: C467.1, U35.4 (OUT_P)
unnamed: C468.1, U35.5 (OUT_N)
unnamed: C469.1, C470.1, L6.2, L7.2, R134.1
unnamed: C471.2, R135.2
unnamed: C472.2, R136.2
unnamed: R80.1, U2.H2 (GTX_RREF)
unnamed: R80.2, U2.H1 (GTX_VTTRCAL)
unnamed: R83.2, U1.U4 (PHY3_LED0)
unnamed: R84.2, U1.V1 (PHY2_LED0)
unnamed: R85.2, U1.U2 (PHY5_LED0)
unnamed: R86.2, U1.U3 (PHY4_LED0)
unnamed: R87.2, U1.T4 (PHY7_LED0)
unnamed: R88.2, U1.U1 (PHY6_LED0)
unnamed: R89.2, U1.T2 (PHY9_LED0)
unnamed: R90.2, U1.T3 (PHY8_LED0)
unnamed: R91.2, U1.R4 (PHY11_LED0)
unnamed: R92.2, U1.T1 (PHY10_LED0)
unnamed: R93.2, U1.AA2 (PHY1_LED1)
unnamed: R94.2, U1.AA3 (PHY0_LED1)
unnamed: R95.2, U1.Y4 (PHY3_LED1)
unnamed: R96.2, U1.AA1 (PHY2_LED1)
unnamed: R97.2, U1.Y2 (PHY5_LED1)
unnamed: R98.2, U1.Y3 (PHY4_LED1)
unnamed: R99.2, U1.W4 (PHY7_LED1)
unnamed: R100.2, U1.Y1 (PHY6_LED1)
unnamed: R101.2, U1.W2 (PHY9_LED1)
unnamed: R102.2, U1.W3 (PHY8_LED1)
unnamed: R103.2, U1.V4 (PHY11_LED1)
unnamed: R104.2, U1.W1 (PHY10_LED1)
unnamed: R105.1, U1.AE22 (SERDES_REXT0)
unnamed: R105.2, U1.AF22 (SERDES_REXT1)
unnamed: R108.2, U1.D21 (JTAG_TRST)
unnamed: R110.2, U1.E13 (REF_REXT1)
unnamed: C353.1, U1.E14 (REF_FILT1)
unnamed: R109.2, U1.K4 (REF_REXT2)
unnamed: R111.2, U1.K23 (REF_REXT0)
unnamed: C352.1, U1.L4 (REF_FILT2)
unnamed: C354.1, U1.L23 (REF_FILT0)
unnamed: R81.2, U1.V2 (PHY1_LED0)
unnamed: R82.2, U1.V3 (PHY0_LED0)

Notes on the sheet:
Polarity swap Invert in FPGA
Refclk is LVDS (must be AC coupled) and internally terminated / biased (Fig. 12 on page 16)
Verify LEDs and diffpairs match up to the same port Verify all pin swaps comply with rules for PHY
ESD protection
Center tap termination capacitors
Can use 156.25 for both Provide a second oscillator footprint just in case
Strap: Refclk is 125 MHz
VSC8512 Hardware Design Checklist Section 8.2 page 23
Open drain
Level shifting for LVCMOS25 GPIOs to FPGA
Per table 5 (page 23) Can swap A/B pairs Can swap C/D pairs But cannot swap A/B with C/D
!!SIGNOFF REVIEW CHECK!!
One LED per RJ45 (bi color) but VSC8512 has two single LED pins
SFP+ power filtering
Strap: PHY addr MSBs = 2'b00
